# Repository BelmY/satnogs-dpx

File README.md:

# SatNOGS Diplexer

Diplexer for SatNOGS project.

Diplexer is used to connect VHF and UHF in the same SDR hardware.

More information about filter in report and qucs project files.

Repository includes all source files for PCB's qucs, simulation files and reports about the filter
specifications.

## Repository policy

SatNOGS hardware repositories only track source design files. All needed derivative files (e.g. grb etc)
for production are created per release, packaged in an archive and uploaded linked to a  [release](https://gitlab.com/librespacefoundation/satnogs/satnogs-diplexer/tags).

Each major release (x.0.0) is branched out of master. Subsequent fixes (minor or not) are commited on those branches and tagged accordingly.

Master branch is most times under active development, so expect things to break. For production ready and previous releases source files check tags and branches.

## Contribute

The main repository lives on [Gitlab](https://gitlab.com/librespacefoundation/satnogs/satnogs-diplexer) and all Merge Request should happen there.

## License

Licensed under the [CERN OHLv1.2](LICENSE).

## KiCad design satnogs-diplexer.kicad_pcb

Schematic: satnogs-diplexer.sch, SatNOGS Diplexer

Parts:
C1, C5: 6.8p; C_0603_1608Metric
C2, C4: 22p; C_0603_1608Metric
C3: 5p; C_0603_1608Metric
L1: 56n; L_0603_1608Metric
L2, L4: 15n; L_0603_1608Metric
L3: 82n; L_0603_1608Metric
L5: 47n; L_0603_1608Metric
P1: SDR; SMA_Amphenol_132289_EdgeMount
P2: VHF; SMA_Amphenol_132289_EdgeMount
P3: UHF; SMA_Amphenol_132289_EdgeMount

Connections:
GND: C2.2, C4.2, L2.2, L4.2, P1.2, P2.2, P3.2
unnamed: C1.1, C3.2, L2.1
unnamed: C1.2, L1.1, P1.1
unnamed: C2.1, L1.2, L3.1
unnamed: C3.1, C5.2, L4.1
unnamed: C4.1, L3.2, L5.1
unnamed: C5.1, P3.1
unnamed: L5.2, P2.1

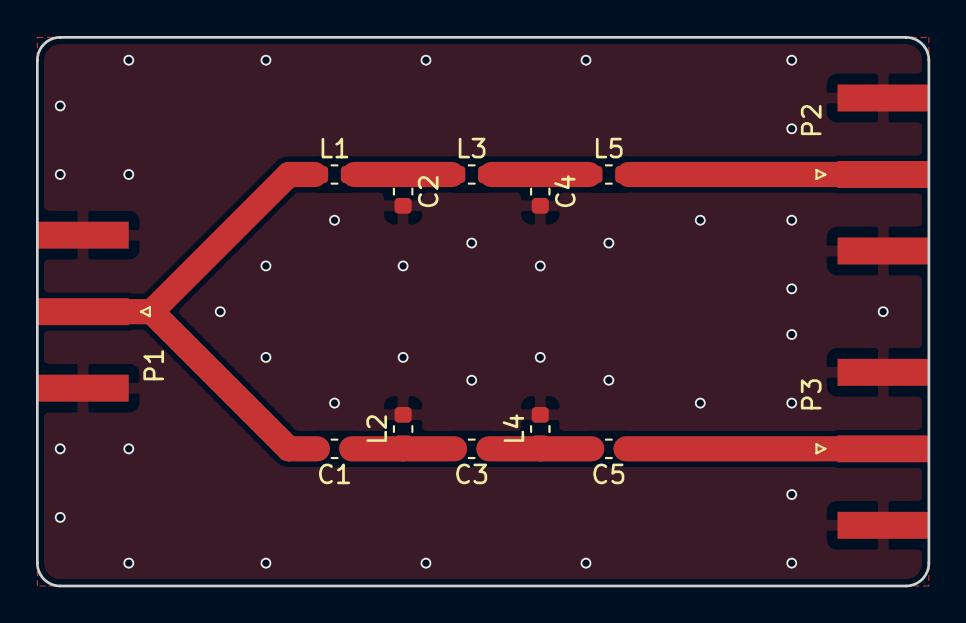
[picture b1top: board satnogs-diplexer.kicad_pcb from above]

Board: 2 copper layers, 49.5 x 30.5 mm, 13 parts (0 on the bottom side), 8 nets.

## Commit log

2015-04-14 Cleanup diplexer repository.
2015-04-24 Update README with license notice
2015-04-27 Update documentation link
2017-07-28 Add kicad and qucs ignore files
2017-07-28 Add kicad files for diplexer
2017-07-28 Add kicad library with rf connector
2017-07-28 Resolve conflict in README.
2017-07-28 Add qucs project and VNA reports
2017-07-28 Update BOM
2017-07-28 Add vias, silksceen to board
2017-09-20 Update files after gitlab migration
2020-02-17 Fix license file to match original text version
2020-02-18 Add Libre Space Foundation Contribution Guide
2020-04-25 FIxes #3
2020-04-25 Remove unuse file and update the copyright badge
